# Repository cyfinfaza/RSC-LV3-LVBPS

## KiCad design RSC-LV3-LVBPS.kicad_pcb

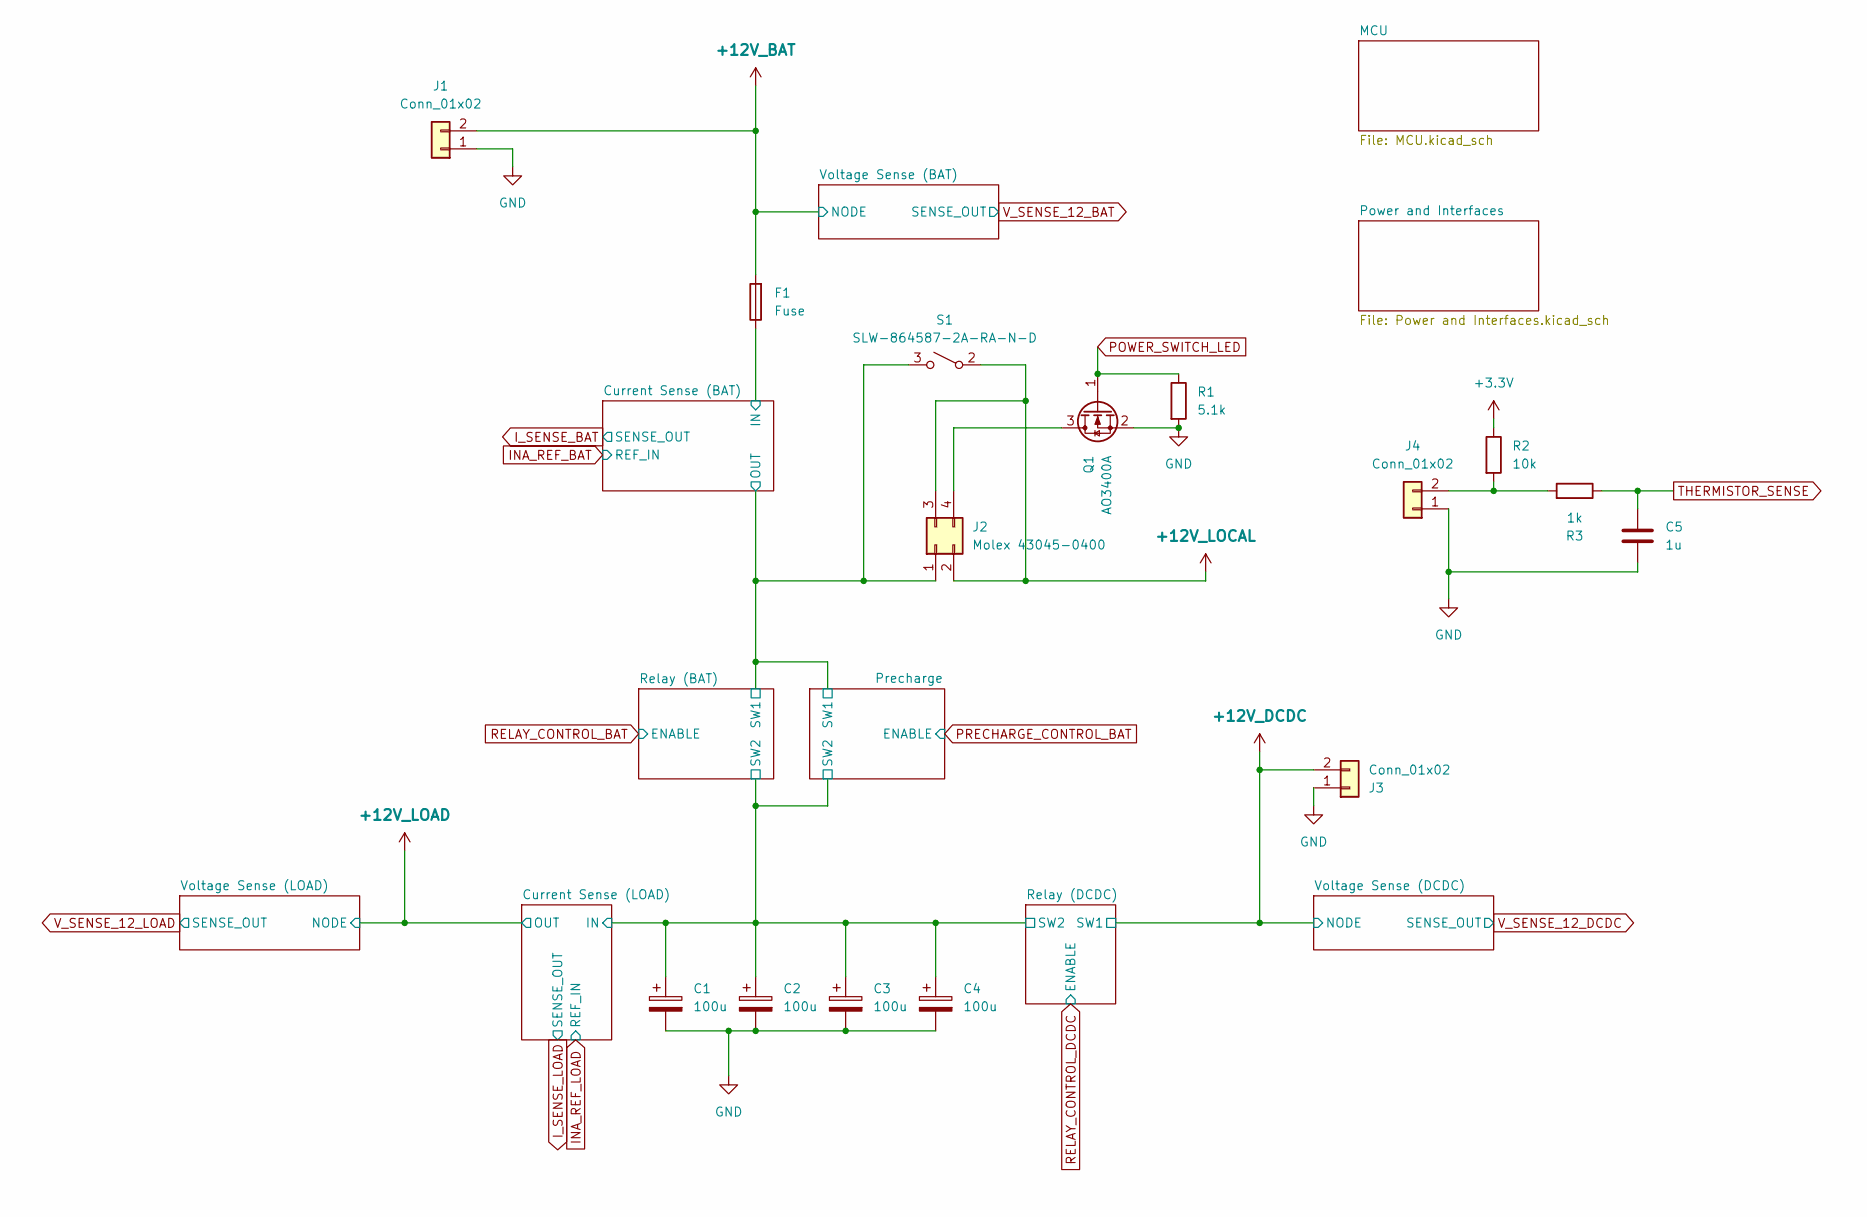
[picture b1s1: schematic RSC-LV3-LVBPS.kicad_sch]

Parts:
C1, C2, C3, C4: 100u; CP_Radial_D6.3mm_P2.50mm
C5: 1u; C_0603_1608Metric_Pad1.08x0.95mm_HandSolder
F1: Fuse; Fuseholder_Blade_Mini_Keystone_3568
J1, J3, J4: Conn_01x02; Molex_Micro-Fit_3.0_43650-0200_1x02_P3.00mm_Horizontal_Vert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
J2: Molex 43045-0400; Molex_Micro-Fit_3.0_43045-0400_2x02_P3.00mm_Horizontal_Vert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
Q1: AO3400A; SOT-23
R1: 5.1k; R_0603_1608Metric_Pad0.98x0.95mm_HandSolder
R2: 10k; R_0603_1608Metric_Pad0.98x0.95mm_HandSolder
R3: 1k; R_0603_1608Metric_Pad0.98x0.95mm_HandSolder
S1: SLW-864587-2A-RA-N-D; SLW8645872ARAND

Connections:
+3.3V: R2.1; also elsewhere on the board
+12V_BAT: F1.2, J1.2; also elsewhere on the board
+12V_DCDC: J3.2; also elsewhere on the board
+12V_LOCAL: J2.2, J2.3, S1.2 (A); also elsewhere on the board
/Current Sense (BAT)/IN: F1.1; also elsewhere on the board
/Current Sense (BAT)/OUT: J2.1, S1.3 (B); also elsewhere on the board
/Current Sense (LOAD)/IN: C1.1, C2.1, C3.1, C4.1; also elsewhere on the board
GND: C1.2, C2.2, C3.2, C4.2, C5.2, J1.1, J3.1, J4.1, Q1.2 (S), R1.2; also elsewhere on the board
unnamed: J2.4, Q1.3 (D)
unnamed: J4.2, R2.2, R3.2
POWER_SWITCH_LED: Q1.1 (G), R1.1; also elsewhere on the board
THERMISTOR_SENSE: C5.1, R3.1; also elsewhere on the board

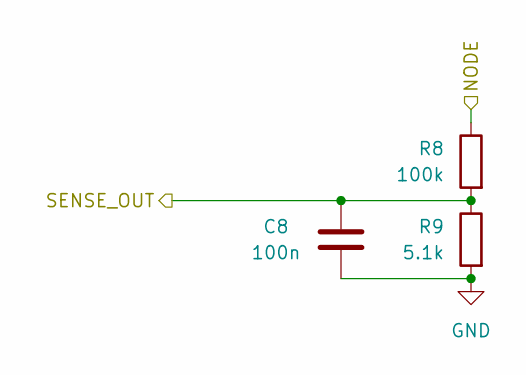
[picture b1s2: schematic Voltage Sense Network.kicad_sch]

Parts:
C8: 100n; C_0603_1608Metric_Pad1.08x0.95mm_HandSolder
R8: 100k; R_0603_1608Metric_Pad0.98x0.95mm_HandSolder
R9: 5.1k; R_0603_1608Metric_Pad0.98x0.95mm_HandSolder

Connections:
+12V_BAT: R8.1; also elsewhere on the board
GND: C8.2, R9.2; also elsewhere on the board
V_SENSE_12_BAT: C8.1, R8.2, R9.1; also elsewhere on the board

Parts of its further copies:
C9, C10: 100n; C_0603_1608Metric_Pad1.08x0.95mm_HandSolder
R12, R14: 100k; R_0603_1608Metric_Pad0.98x0.95mm_HandSolder
R13, R15: 5.1k; R_0603_1608Metric_Pad0.98x0.95mm_HandSolder

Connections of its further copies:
+12V_DCDC: R14.1; also elsewhere on the board
+12V_LOAD: R12.1; also elsewhere on the board
GND: C9.2, C10.2, R13.2, R15.2; also elsewhere on the board
V_SENSE_12_DCDC: C10.1, R14.2, R15.1; also elsewhere on the board
V_SENSE_12_LOAD: C9.1, R12.2, R13.1; also elsewhere on the board

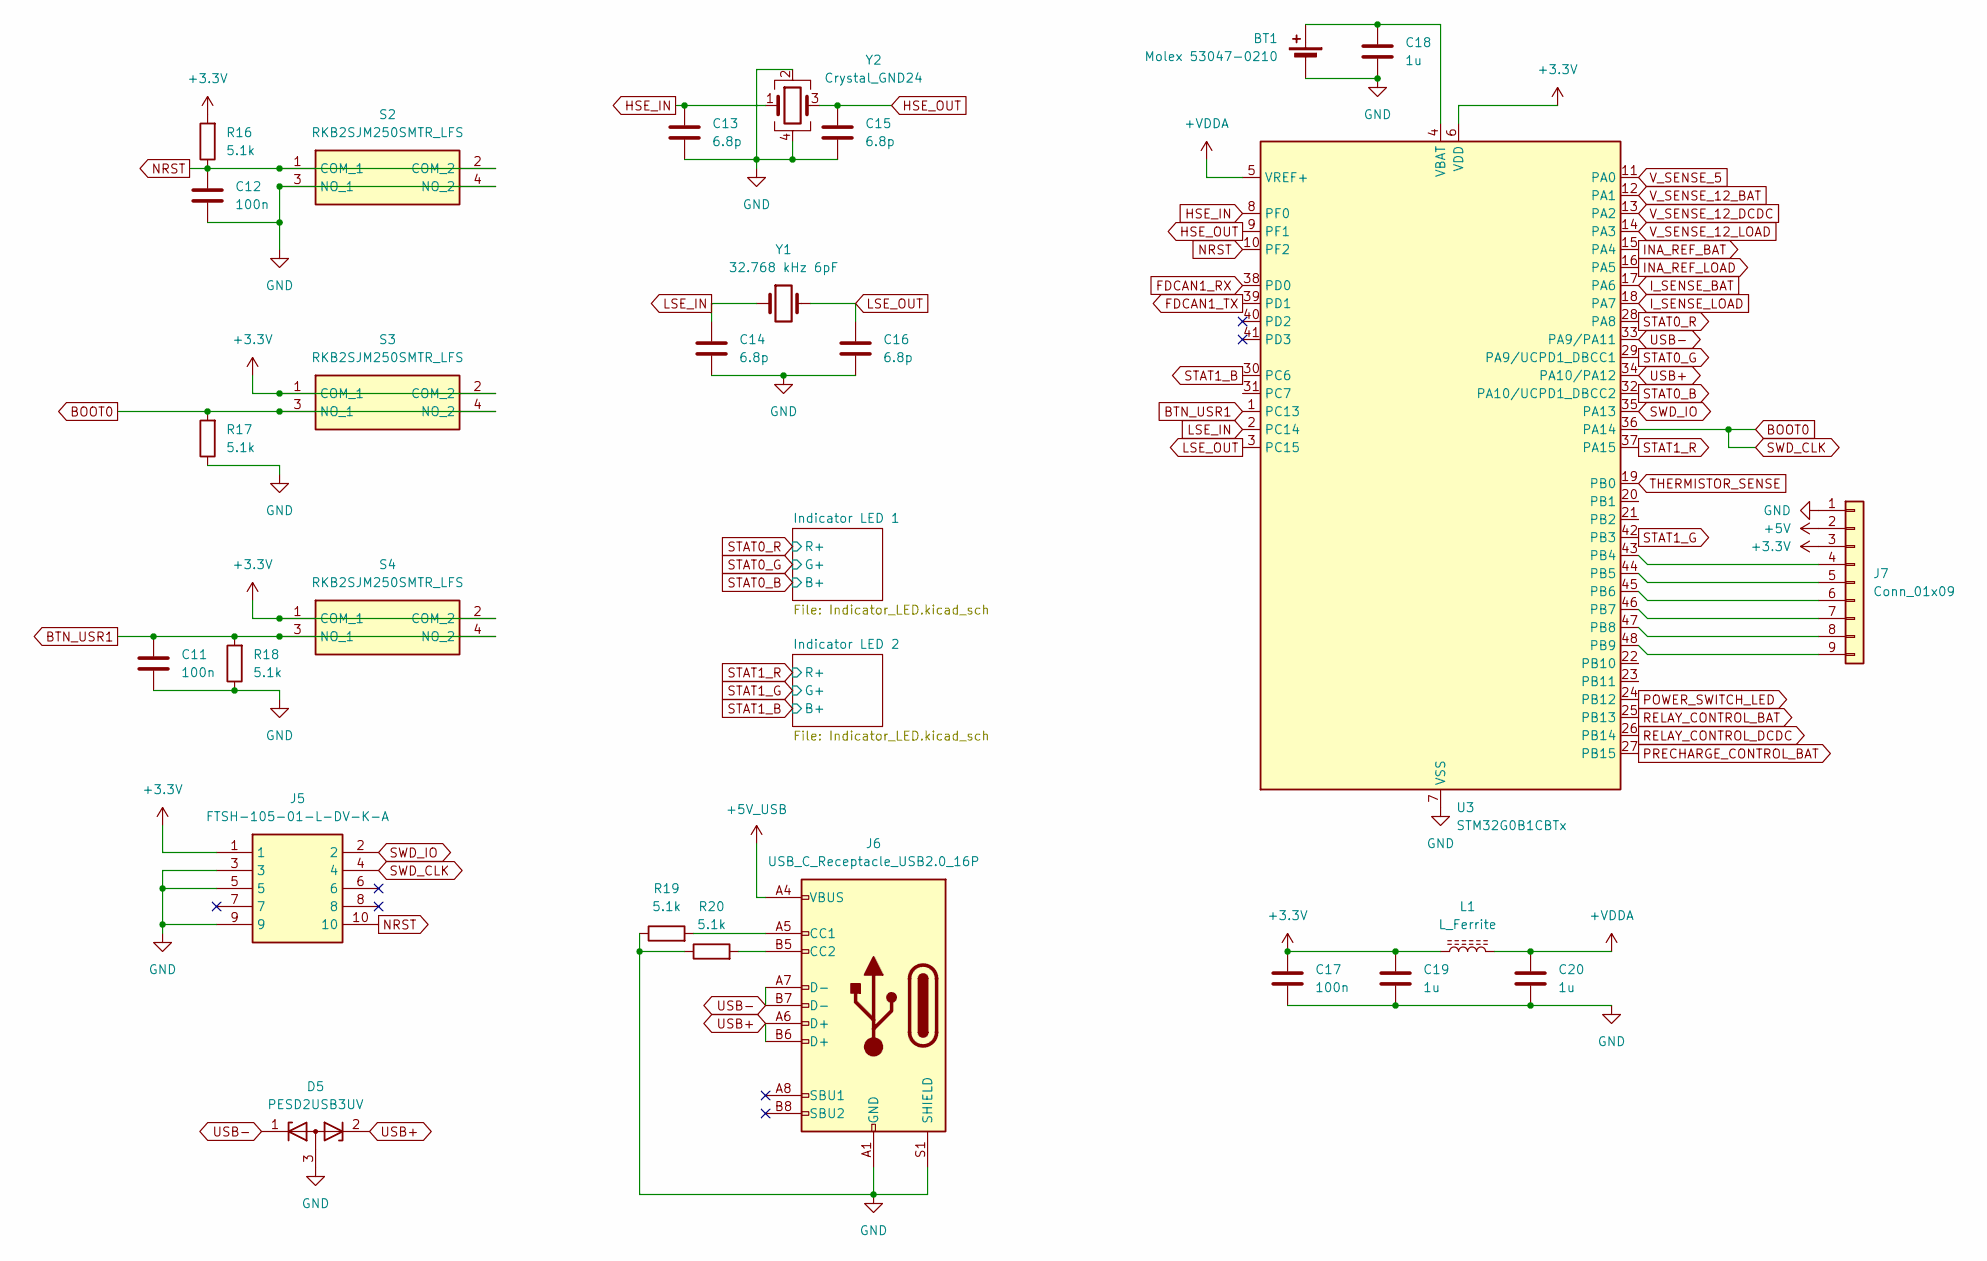
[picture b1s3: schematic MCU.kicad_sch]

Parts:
BT1: Molex 53047-0210; Molex_PicoBlade_53047-0210_1x02_P1.25mm_Vertical
C11, C12, C17: 100n; C_0603_1608Metric_Pad1.08x0.95mm_HandSolder
C13, C14, C15, C16: 6.8p; C_0603_1608Metric_Pad1.08x0.95mm_HandSolder
C18, C19, C20: 1u; C_0603_1608Metric_Pad1.08x0.95mm_HandSolder
D5: PESD2USB3UV; SOT-23W
J5: FTSH-105-01-L-DV-K-A; FTSH-105-XX-YYY-DV-K-A; Mouser Part Number 200-FTSH10501LDVKA
J6: USB_C_Receptacle_USB2.0_16P; USB_C_Receptacle_HRO_TYPE-C-31-M-12
J7: Conn_01x09; PinHeader_1x09_P2.54mm_Vertical
L1: L_Ferrite; L_0603_1608Metric_Pad1.05x0.95mm_HandSolder
R16, R17, R18, R19, R20: 5.1k; R_0603_1608Metric_Pad0.98x0.95mm_HandSolder
S2, S3, S4: RKB2SJM250SMTR_LFS; RKB2SJM250SMTRLFS; Mouser Part Number 611-RKB2SJM250SMTRLF
U3: STM32G0B1CBTx; LQFP-48_7x7mm_P0.5mm
Y1: 32.768 kHz 6pF; Crystal_C26-LF_D2.1mm_L6.5mm_Horizontal
Y2: Crystal_GND24; Crystal_SMD_3225-4Pin_3.2x2.5mm

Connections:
+3.3V: C17.1, C19.1, J5.1, J7.3, L1.1, R16.2, S3.1 (COM_1), S3.2 (COM_2), S4.1 (COM_1), S4.2 (COM_2), U3.6 (VDD); also elsewhere on the board
+5V: J7.2; also elsewhere on the board
+5V_USB: J6.A4 (VBUS), J6.A9 (VBUS), J6.B4 (VBUS), J6.B9 (VBUS); also elsewhere on the board
+VDDA: C20.1, L1.2, U3.5 (VREF+)
BOOT0: J5.4, R17.2, S3.3 (NO_1), S3.4 (NO_2), U3.36 (PA14)
BTN_USR1: C11.1, R18.2, S4.3 (NO_1), S4.4 (NO_2), U3.1 (PC13)
FDCAN1_RX: U3.38 (PD0); also elsewhere on the board
FDCAN1_TX: U3.39 (PD1); also elsewhere on the board
GND: BT1.2 (-), C11.2, C12.2, C13.2, C14.2, C15.2, C16.2, C17.2, C18.2, C19.2, C20.2, D5.3 (A), J5.3, J5.5, J5.9, J6.A1 (GND), J6.A12 (GND), J6.B1 (GND), J6.B12 (GND), J6.S1 (SHIELD), J7.1, R17.1, R18.1, R19.1, R20.1, S2.3 (NO_1), S2.4 (NO_2), U3.7 (VSS), Y2.2, Y2.4; also elsewhere on the board
HSE_IN: C13.1, U3.8 (PF0), Y2.1
HSE_OUT: C15.1, U3.9 (PF1), Y2.3
INA_REF_BAT: U3.15 (PA4); also elsewhere on the board
INA_REF_LOAD: U3.16 (PA5); also elsewhere on the board
I_SENSE_BAT: U3.17 (PA6); also elsewhere on the board
I_SENSE_LOAD: U3.18 (PA7); also elsewhere on the board
LSE_IN: C14.1, U3.2 (PC14), Y1.1
LSE_OUT: C16.1, U3.3 (PC15), Y1.2
NRST: C12.1, J5.10, R16.1, S2.1 (COM_1), S2.2 (COM_2), U3.10 (PF2)
unnamed: BT1.1 (+), C18.1, U3.4 (VBAT)
unnamed: J6.A5 (CC1), R19.2
unnamed: J6.B5 (CC2), R20.2
unnamed: J7.4, U3.43 (PB4)
unnamed: J7.5, U3.44 (PB5)
unnamed: J7.6, U3.45 (PB6)
unnamed: J7.7, U3.46 (PB7)
unnamed: J7.8, U3.47 (PB8)
unnamed: J7.9, U3.48 (PB9)
POWER_SWITCH_LED: U3.24 (PB12); also elsewhere on the board
PRECHARGE_CONTROL_BAT: U3.27 (PB15); also elsewhere on the board
RELAY_CONTROL_BAT: U3.25 (PB13); also elsewhere on the board
RELAY_CONTROL_DCDC: U3.26 (PB14); also elsewhere on the board
STAT0_B: U3.32 (PA10/UCPD1_DBCC2); also elsewhere on the board
STAT0_G: U3.29 (PA9/UCPD1_DBCC1); also elsewhere on the board
STAT0_R: U3.28 (PA8); also elsewhere on the board
STAT1_B: U3.30 (PC6); also elsewhere on the board
STAT1_G: U3.42 (PB3); also elsewhere on the board
STAT1_R: U3.37 (PA15); also elsewhere on the board
SWD_IO: J5.2, U3.35 (PA13)
THERMISTOR_SENSE: U3.19 (PB0); also elsewhere on the board
USB+: D5.2 (K), J6.A6 (D+), J6.B6 (D+), U3.34 (PA10/PA12)
USB-: D5.1 (K), J6.A7 (D-), J6.B7 (D-), U3.33 (PA9/PA11)
V_SENSE_5: U3.11 (PA0); also elsewhere on the board
V_SENSE_12_BAT: U3.12 (PA1); also elsewhere on the board
V_SENSE_12_DCDC: U3.13 (PA2); also elsewhere on the board
V_SENSE_12_LOAD: U3.14 (PA3); also elsewhere on the board

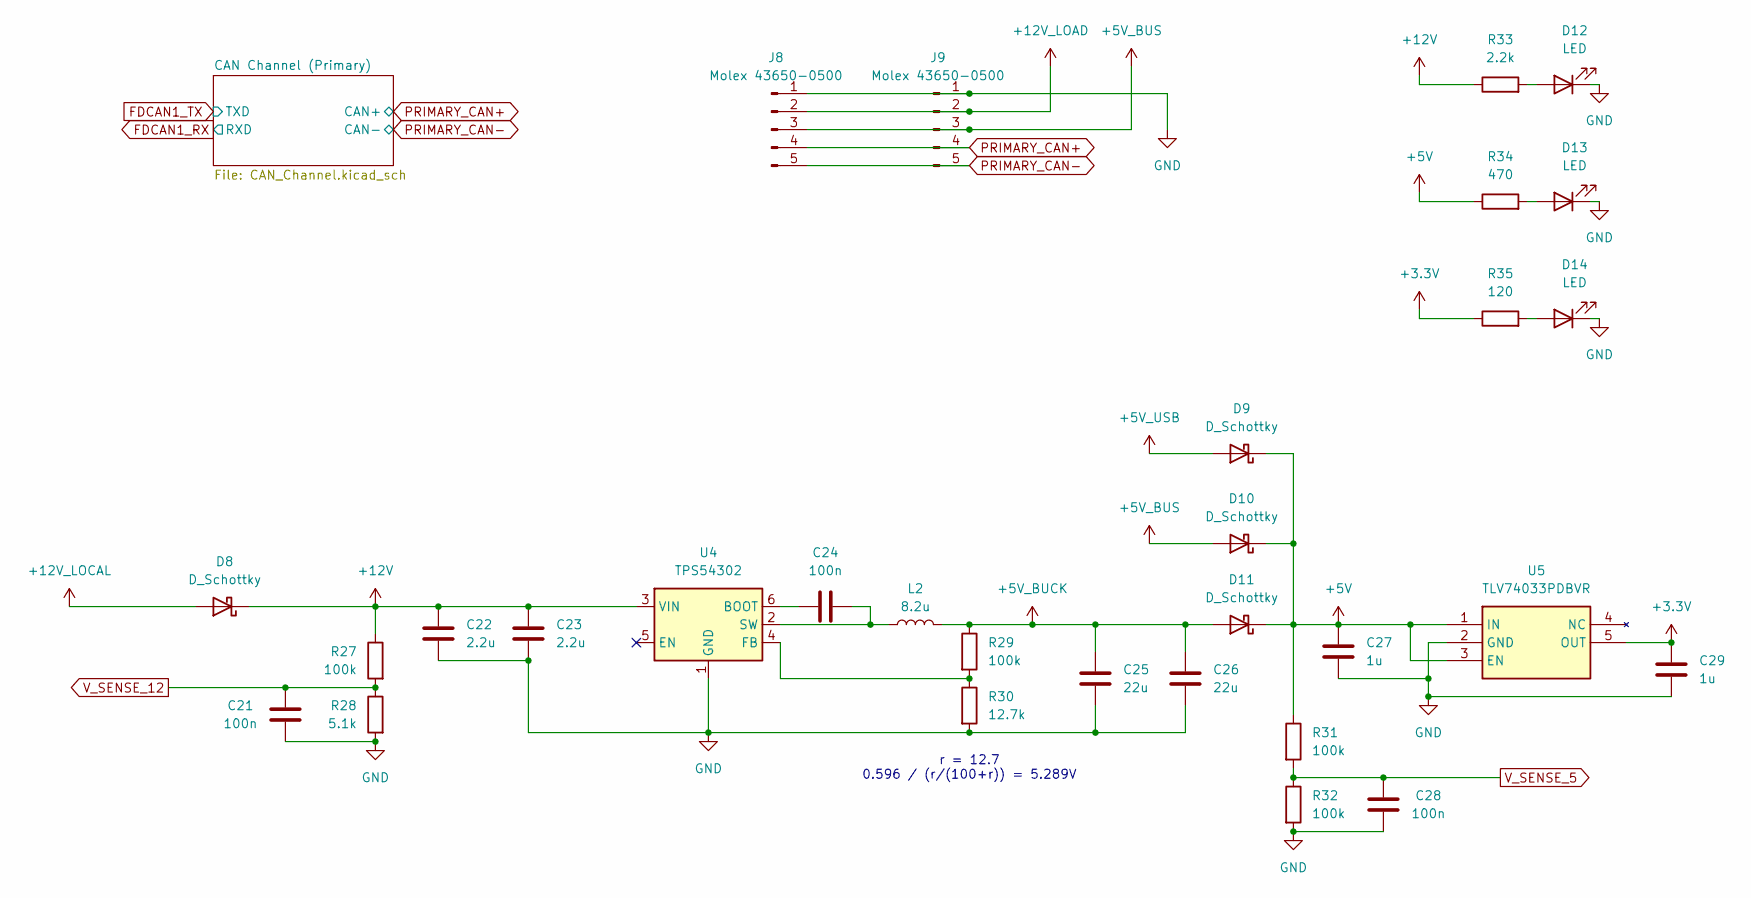
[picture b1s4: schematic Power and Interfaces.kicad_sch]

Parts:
C21, C24, C28: 100n; C_0603_1608Metric_Pad1.08x0.95mm_HandSolder
C22, C23: 2.2u; C_0603_1608Metric_Pad1.08x0.95mm_HandSolder
C25, C26: 22u; C_1206_3216Metric_Pad1.33x1.80mm_HandSolder
C27, C29: 1u; C_0603_1608Metric_Pad1.08x0.95mm_HandSolder
D8, D9, D10, D11: D_Schottky; D_SOD-123F
D12, D13, D14: LED; LED_0603_1608Metric_Pad1.05x0.95mm_HandSolder
J8, J9: Molex 43650-0500; Molex_Micro-Fit_3.0_43650-0500_1x05_P3.00mm_Horizontal_Vert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
L2: 8.2u; L_Abracon_ASPI-4030S
R27, R29, R31, R32: 100k; R_0603_1608Metric_Pad0.98x0.95mm_HandSolder
R28: 5.1k; R_0603_1608Metric_Pad0.98x0.95mm_HandSolder
R30: 12.7k; R_0603_1608Metric_Pad0.98x0.95mm_HandSolder
R33: 2.2k; R_0603_1608Metric_Pad0.98x0.95mm_HandSolder
R34: 470; R_0603_1608Metric_Pad0.98x0.95mm_HandSolder
R35: 120; R_0603_1608Metric_Pad0.98x0.95mm_HandSolder
U4: TPS54302; SOT-23-6_Handsoldering
U5: TLV74033PDBVR; SOT95P280X145-5N; Mouser Part Number 595-TLV74033PDBVR

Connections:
+3.3V: C29.1, R35.1, U5.5 (OUT); also elsewhere on the board
+5V: C27.1, D9.1 (K), D10.1 (K), D11.1 (K), R31.1, R34.1, U5.1 (IN), U5.3 (EN); also elsewhere on the board
+5V_BUCK: C25.1, C26.1, D11.2 (A), L2.2, R29.1
+5V_BUS: D10.2 (A), J8.3, J9.3
+5V_USB: D9.2 (A); also elsewhere on the board
+12V: C22.1, C23.1, D8.1 (K), R27.1, R33.1, U4.3 (VIN)
+12V_LOAD: J8.2, J9.2; also elsewhere on the board
+12V_LOCAL: D8.2 (A); also elsewhere on the board
GND: C21.2, C22.2, C23.2, C25.2, C26.2, C27.2, C28.2, C29.2, D12.1 (K), D13.1 (K), D14.1 (K), J8.1, J9.1, R28.2, R30.2, R32.2, U4.1 (GND), U5.2 (GND); also elsewhere on the board
unnamed: D12.2 (A), R33.2
unnamed: D13.2 (A), R34.2
unnamed: D14.2 (A), R35.2
unnamed: C24.1, U4.6 (BOOT)
unnamed: R29.2, R30.1, U4.4 (FB)
unnamed: C24.2, L2.1, U4.2 (SW)
PRIMARY_CAN+: J8.4, J9.4; also elsewhere on the board
PRIMARY_CAN-: J8.5, J9.5; also elsewhere on the board
V_SENSE_5: C28.1, R31.2, R32.1; also elsewhere on the board
V_SENSE_12: C21.1, R27.2, R28.1

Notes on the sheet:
r = 12.7 0.596 / (r/(100+r)) = 5.289V

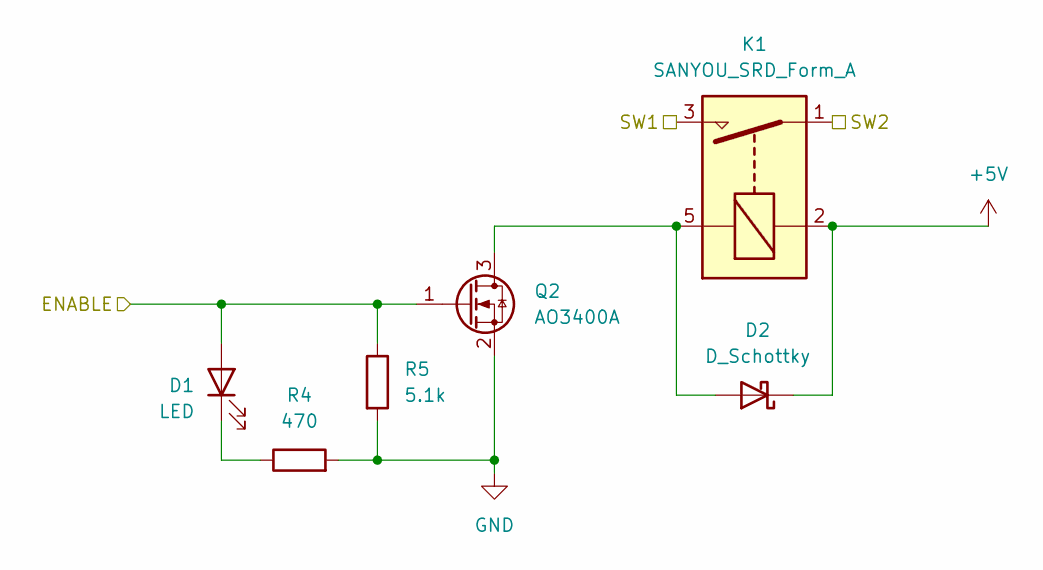
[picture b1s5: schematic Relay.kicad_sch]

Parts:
D1: LED; LED_0603_1608Metric_Pad1.05x0.95mm_HandSolder
D2: D_Schottky; D_SOD-123F
K1: SANYOU_SRD_Form_A; Relay_SPST_SANYOU_SRD_Series_Form_A
Q2: AO3400A; SOT-23
R4: 470; R_0603_1608Metric_Pad0.98x0.95mm_HandSolder
R5: 5.1k; R_0603_1608Metric_Pad0.98x0.95mm_HandSolder

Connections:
+5V: D2.1 (K), K1.2; also elsewhere on the board
+12V_DCDC: K1.3; also elsewhere on the board
/Current Sense (LOAD)/IN: K1.1; also elsewhere on the board
GND: Q2.2 (S), R4.2, R5.2; also elsewhere on the board
unnamed: D1.1 (K), R4.1
unnamed: D2.2 (A), K1.5, Q2.3 (D)
RELAY_CONTROL_DCDC: D1.2 (A), Q2.1 (G), R5.1; also elsewhere on the board

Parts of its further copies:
D3: LED; LED_0603_1608Metric_Pad1.05x0.95mm_HandSolder
D4: D_Schottky; D_SOD-123F
K2: SANYOU_SRD_Form_A; Relay_SPST_SANYOU_SRD_Series_Form_A
Q3: AO3400A; SOT-23
R10: 470; R_0603_1608Metric_Pad0.98x0.95mm_HandSolder
R11: 5.1k; R_0603_1608Metric_Pad0.98x0.95mm_HandSolder

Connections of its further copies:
+5V: D4.1 (K), K2.2; also elsewhere on the board
/Current Sense (BAT)/OUT: K2.3; also elsewhere on the board
/Current Sense (LOAD)/IN: K2.1; also elsewhere on the board
GND: Q3.2 (S), R10.2, R11.2; also elsewhere on the board
unnamed: D3.1 (K), R10.1
unnamed: D4.2 (A), K2.5, Q3.3 (D)
RELAY_CONTROL_BAT: D3.2 (A), Q3.1 (G), R11.1; also elsewhere on the board

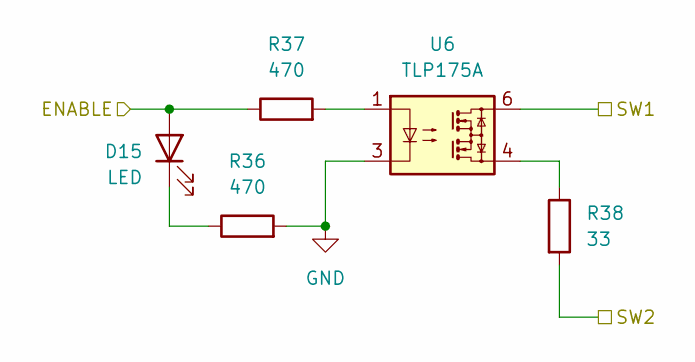
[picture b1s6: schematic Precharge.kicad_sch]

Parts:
D15: LED; LED_0603_1608Metric_Pad1.05x0.95mm_HandSolder
R36, R37: 470; R_0603_1608Metric_Pad0.98x0.95mm_HandSolder
R38: 33; R_2512_6332Metric
U6: TLP175A; Toshiba_SOIC-4-6_4.4x3.6mm_P1.27mm

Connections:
/Current Sense (BAT)/OUT: U6.6; also elsewhere on the board
/Current Sense (LOAD)/IN: R38.2; also elsewhere on the board
GND: R36.2, U6.3; also elsewhere on the board
unnamed: D15.1 (K), R36.1
unnamed: R37.2, U6.1
unnamed: R38.1, U6.4
PRECHARGE_CONTROL_BAT: D15.2 (A), R37.1; also elsewhere on the board

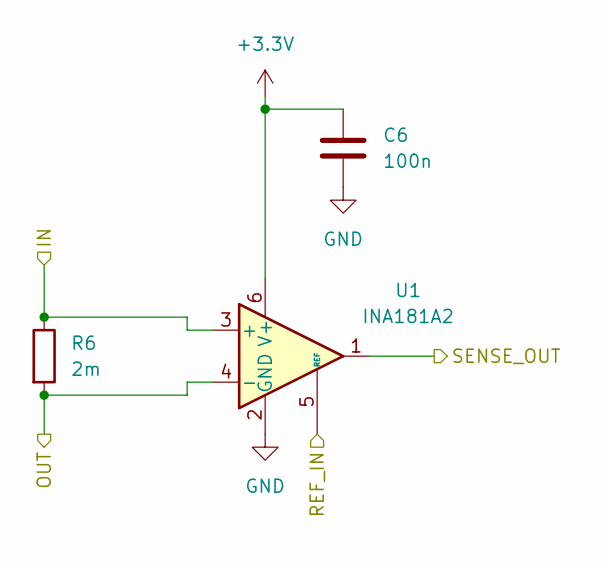
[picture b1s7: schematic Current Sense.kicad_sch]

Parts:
C6: 100n; C_0603_1608Metric_Pad1.08x0.95mm_HandSolder
R6: 2m; R_1206_3216Metric_Pad1.30x1.75mm_HandSolder
U1: INA181A2; SOT-23-6_Handsoldering

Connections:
+3.3V: C6.1, U1.6 (V+); also elsewhere on the board
/Current Sense (BAT)/IN: R6.1, U1.3 (+); also elsewhere on the board
/Current Sense (BAT)/OUT: R6.2, U1.4 (-); also elsewhere on the board
GND: C6.2, U1.2 (GND); also elsewhere on the board
INA_REF_BAT: U1.5 (REF); also elsewhere on the board
I_SENSE_BAT: U1.1; also elsewhere on the board

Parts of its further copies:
C7: 100n; C_0603_1608Metric_Pad1.08x0.95mm_HandSolder
R7: 2m; R_1206_3216Metric_Pad1.30x1.75mm_HandSolder
U2: INA181A2; SOT-23-6_Handsoldering

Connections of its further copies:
+3.3V: C7.1, U2.6 (V+); also elsewhere on the board
+12V_LOAD: R7.2, U2.4 (-); also elsewhere on the board
/Current Sense (LOAD)/IN: R7.1, U2.3 (+); also elsewhere on the board
GND: C7.2, U2.2 (GND); also elsewhere on the board
INA_REF_LOAD: U2.5 (REF); also elsewhere on the board
I_SENSE_LOAD: U2.1; also elsewhere on the board

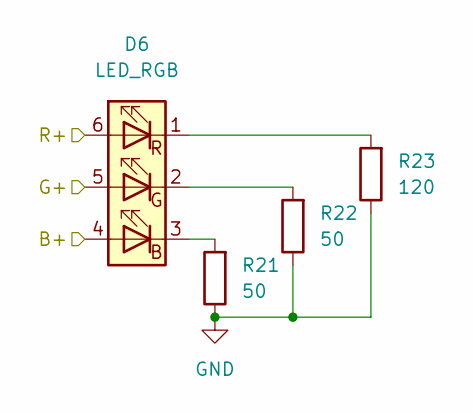
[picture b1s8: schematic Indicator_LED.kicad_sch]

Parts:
D6: LED_RGB; LED_RGB_5050-6
R21, R22: 50; R_0603_1608Metric_Pad0.98x0.95mm_HandSolder
R23: 120; R_0603_1608Metric_Pad0.98x0.95mm_HandSolder

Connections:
GND: R21.1, R22.1, R23.1; also elsewhere on the board
unnamed: D6.3 (BK), R21.2
unnamed: D6.2 (GK), R22.2
unnamed: D6.1 (RK), R23.2
STAT0_B: D6.4 (BA); also elsewhere on the board
STAT0_G: D6.5 (GA); also elsewhere on the board
STAT0_R: D6.6 (RA); also elsewhere on the board

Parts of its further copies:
D7: LED_RGB; LED_RGB_5050-6
R24, R25: 50; R_0603_1608Metric_Pad0.98x0.95mm_HandSolder
R26: 120; R_0603_1608Metric_Pad0.98x0.95mm_HandSolder

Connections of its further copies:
GND: R24.1, R25.1, R26.1; also elsewhere on the board
unnamed: D7.3 (BK), R24.2
unnamed: D7.2 (GK), R25.2
unnamed: D7.1 (RK), R26.2
STAT1_B: D7.4 (BA); also elsewhere on the board
STAT1_G: D7.5 (GA); also elsewhere on the board
STAT1_R: D7.6 (RA); also elsewhere on the board

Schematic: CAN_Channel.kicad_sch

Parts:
C30, C31: 100n; C_0603_1608Metric_Pad1.08x0.95mm_HandSolder
C32: 1u; C_0603_1608Metric_Pad1.08x0.95mm_HandSolder
R39: 120; R_0603_1608Metric_Pad0.98x0.95mm_HandSolder
S5: SLW-864587-2A-RA-N-D; SLW8645872ARAND; Mouser Part Number 179-SLW8645872ARAND
U7: TJA1051T-3; SOIC-8_3.9x4.9mm_P1.27mm

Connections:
+3.3V: C30.1, U7.5 (VIO); also elsewhere on the board
+5V: C31.1, C32.1, U7.3 (VCC); also elsewhere on the board
FDCAN1_RX: U7.4 (RXD); also elsewhere on the board
FDCAN1_TX: U7.1 (TXD); also elsewhere on the board
GND: C30.2, C31.2, C32.2, U7.2 (GND), U7.8 (S); also elsewhere on the board
unnamed: R39.2, S5.3 (NO)
PRIMARY_CAN+: R39.1, U7.7 (CANH); also elsewhere on the board
PRIMARY_CAN-: S5.2 (COM), U7.6 (CANL); also elsewhere on the board

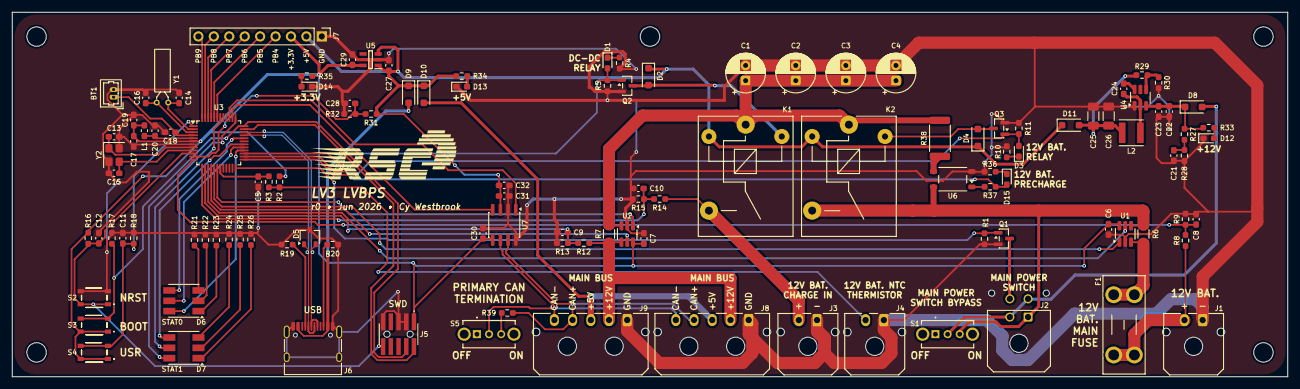
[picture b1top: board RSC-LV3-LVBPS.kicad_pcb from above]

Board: 2 copper layers, 210.0 x 60.0 mm, 118 parts (0 on the bottom side), 80 nets.

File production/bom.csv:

Designator,Footprint,Quantity,Value,LCSC Part #
BT1,Molex_PicoBlade_53047-0210_1x02_P1.25mm_Vertical,1,Molex 53047-0210,
"C1, C2, C3, C4",CP_Radial_D6.3mm_P2.50mm,4,100u,
"C10, C11, C12, C17, C21, C24, C28, C30, C31, C6, C7, C8, C9",0603,13,100n,
"C13, C14, C15, C16",0603,4,6.8p,
"C18, C19, C20, C27, C29, C32, C5",0603,7,1u,
"C22, C23",0603,2,2.2u,
"C25, C26",1206,2,22u,
"D1, D12, D13, D14, D15, D3",0603,6,LED,
"D10, D11, D2, D4, D8, D9",D_SOD-123F,6,D_Schottky,
D5,SOT-23W,1,PESD2USB3UV,
"D6, D7",LED_RGB_5050-6,2,LED_RGB,
F1,Fuseholder_Blade_Mini_Keystone_3568,1,Fuse,
"J1, J3, J4",Molex_Micro-Fit_3.0_43650-0200_1x02_P3.00mm_Horizontal_VerticalCompatible,3,Conn_01x02,
J2,Molex_Micro-Fit_3.0_43045-0400_2x02_P3.00mm_Horizontal_VerticalCompatible,1,Molex 43045-0400,
J5,FTSH-105-XX-YYY-DV-K-A,1,FTSH-105-01-L-DV-K-A,
J6,USB_C_Receptacle_HRO_TYPE-C-31-M-12,1,USB_C_Receptacle_USB2.0_16P,
J7,PinHeader_1x09_P2.54mm_Vertical,1,Conn_01x09,
"J8, J9",Molex_Micro-Fit_3.0_43650-0500_1x05_P3.00mm_Horizontal_VerticalCompatible,2,Molex 43650-0500,
"K1, K2",Relay_SPST_SANYOU_SRD_Series_Form_A,2,SANYOU_SRD_Form_A,
L1,0603,1,L_Ferrite,
L2,L_Abracon_ASPI-4030S,1,8.2u,
"Q1, Q2, Q3",SOT-23,3,AO3400A,
"R1, R11, R13, R15, R16, R17, R18, R19, R20, R28, R5, R9",0603,12,5.1k,
"R10, R34, R36, R37, R4",0603,5,470,
"R12, R14, R27, R29, R31, R32, R8",0603,7,100k,
R2,0603,1,10k,
"R21, R22, R24, R25",0603,4,50,
"R23, R26, R35, R39",0603,4,120,
R3,0603,1,1k,
R30,0603,1,12.7k,
R33,0603,1,2.2k,
R38,2512,1,33,
"R6, R7",1206,2,2m,
"S1, S5",SLW8645872ARAND,2,SLW-864587-2A-RA-N-D,
"S2, S3, S4",RKB2SJM250SMTRLFS,3,RKB2SJM250SMTR_LFS,
"U1, U2",SOT-23-6_Handsoldering,2,INA181A2,
U3,LQFP-48_7x7mm_P0.5mm,1,STM32G0B1CBTx,
U4,SOT-23-6_Handsoldering,1,TPS54302,
U5,SOT95P280X145-5N,1,TLV74033PDBVR,
U6,Toshiba_SOIC-4-6_4.4x3.6mm_P1.27mm,1,TLP175A,
U7,SOIC-8_3.9x4.9mm_P1.27mm,1,TJA1051T-3,
Y1,Crystal_C26-LF_D2.1mm_L6.5mm_Horizontal,1,32.768 kHz 6pF,
Y2,Crystal_SMD_3225-4Pin_3.2x2.5mm,1,Crystal_GND24,

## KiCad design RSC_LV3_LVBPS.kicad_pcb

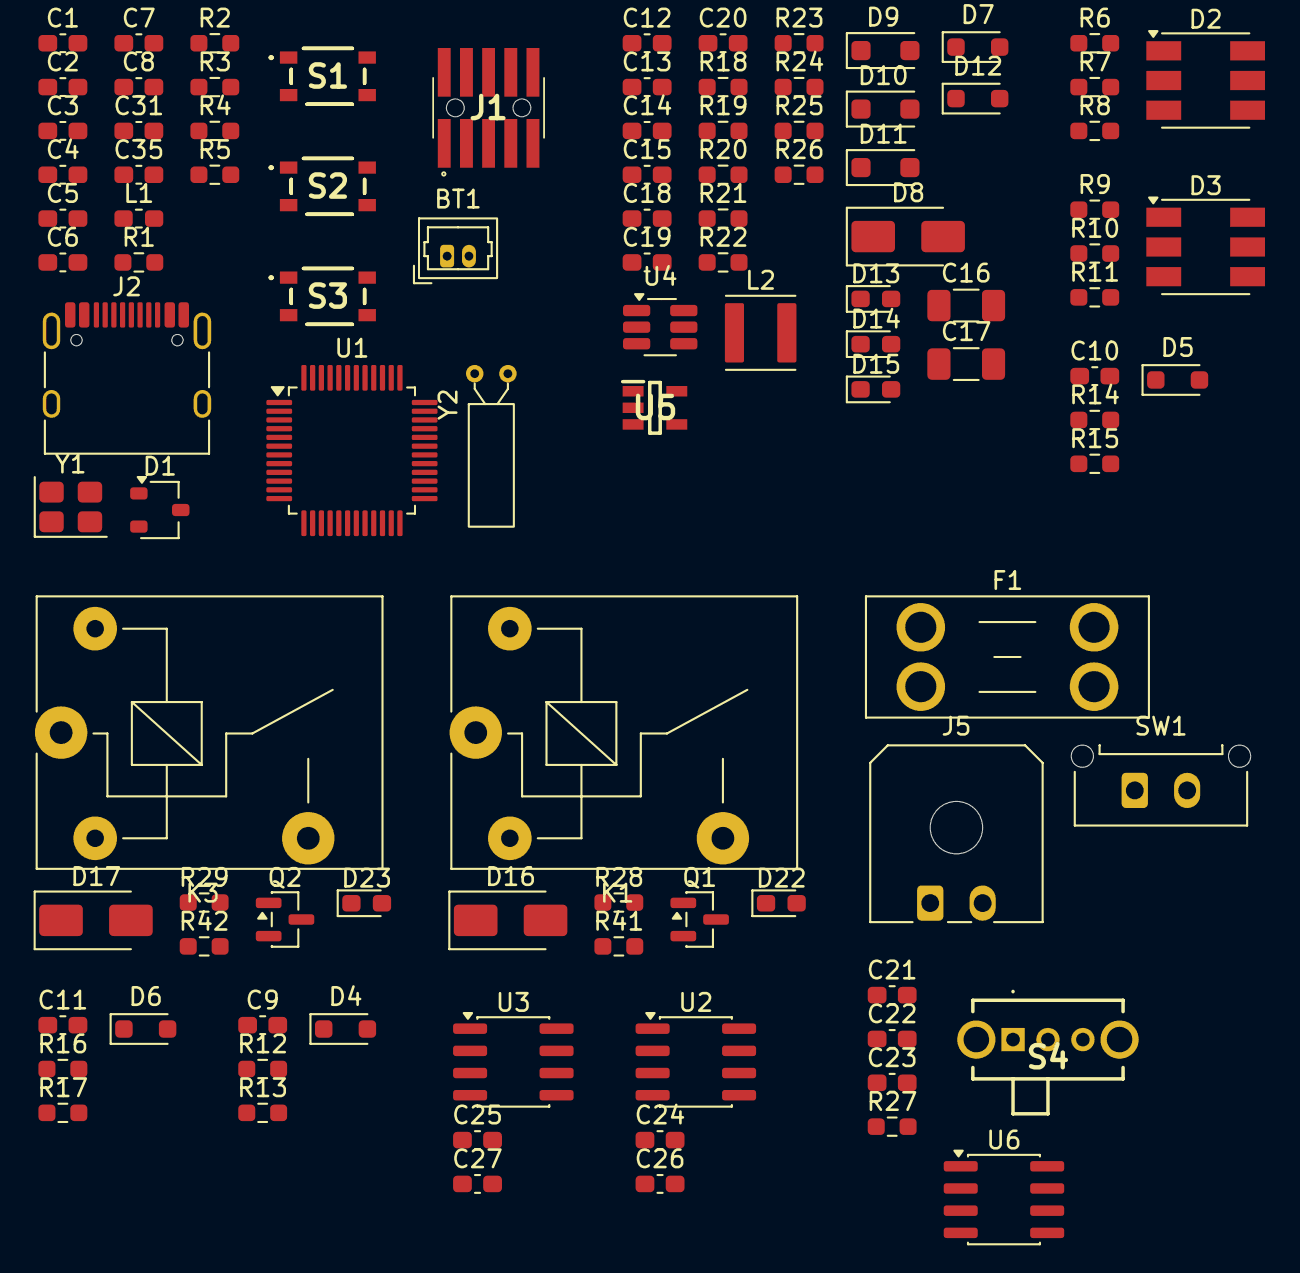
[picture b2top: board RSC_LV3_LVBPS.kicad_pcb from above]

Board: 2 copper layers, 103 parts (0 on the bottom side), 62 nets, no tracks yet.

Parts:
BT1: Molex 53047-0210; Molex_PicoBlade_53047-0210_1x02_P1.25mm_Vertical
C1, C2, C5, C9, C10, C11, C12, C15, C19, C21, C22, C24, C25: 100n; C_0603_1608Metric_Pad1.08x0.95mm_HandSolder
C3, C4, C8, C31: 6.8p; C_0603_1608Metric_Pad1.08x0.95mm_HandSolder
C6, C7, C18, C20, C23, C35: 1u; C_0603_1608Metric_Pad1.08x0.95mm_HandSolder
C13, C14: 2.2u; C_0603_1608Metric_Pad1.08x0.95mm_HandSolder
C16, C17: 22u; C_1206_3216Metric_Pad1.33x1.80mm_HandSolder
C26, C27: 1n; C_0603_1608Metric_Pad1.08x0.95mm_HandSolder
D1: PESD2USB3UV; SOT-23W
D2, D3: LED_RGB; LED_RGB_5050-6
D4, D5, D6, D7, D12: D_Zener; D_SOD-323_HandSoldering
D8, D16, D17: D_Schottky; D_SMA
D9, D10, D11: D_Schottky; D_SOD-123F
D13, D14, D15, D22, D23: LED; LED_0603_1608Metric_Pad1.05x0.95mm_HandSolder
F1: Fuse; Fuseholder_Blade_Mini_Keystone_3568
J1: FTSH-105-01-L-DV-K-A; FTSH-105-XX-YYY-DV-K-A
J2: USB_C_Receptacle_USB2.0_16P; USB_C_Receptacle_HRO_TYPE-C-31-M-12
J5: Conn_01x02; Molex_Micro-Fit_3.0_43650-0200_1x02_P3.00mm_Horizontal
K1, K3: Relay_SPST-NO; Relay_SPST_SANYOU_SRD_Series_Form_A
L1: L_Ferrite; L_0603_1608Metric_Pad1.05x0.95mm_HandSolder
L2: 8.2u; L_Abracon_ASPI-4030S
Q1, Q2: AO3400A; SOT-23
R1, R2, R3, R4, R5, R13, R15, R17, R19, R28, R29: 5.1k; R_0603_1608Metric_Pad0.98x0.95mm_HandSolder
R6, R7, R9, R10: 50; R_0603_1608Metric_Pad0.98x0.95mm_HandSolder
R8, R11, R26, R27: 120; R_0603_1608Metric_Pad0.98x0.95mm_HandSolder
R12, R14, R16, R18, R20, R22, R23: 100k; R_0603_1608Metric_Pad0.98x0.95mm_HandSolder
R21: 12.7k; R_0603_1608Metric_Pad0.98x0.95mm_HandSolder
R24: 2.2k; R_0603_1608Metric_Pad0.98x0.95mm_HandSolder
R25, R41, R42: 470; R_0603_1608Metric_Pad0.98x0.95mm_HandSolder
S1, S2, S3: RKB2SJM250SMTR_LFS; RKB2SJM250SMTRLFS
S4: SLW-864587-2A-RA-N-D; SLW8645872ARAND
SW1: SW_SPST; Molex_Micro-Fit_3.0_43650-0215_1x02_P3.00mm_Vertical
U1: STM32G0B1CBTx; LQFP-48_7x7mm_P0.5mm
U2, U3: ACS711xLCTR-12AB; SOIC-8_3.9x4.9mm_P1.27mm
U4: TPS54302; SOT-23-6_Handsoldering
U5: TLV74033PDBVR; SOT95P280X145-5N
U6: TJA1051T-3; SOIC-8_3.9x4.9mm_P1.27mm
Y1: Crystal_GND24; Crystal_SMD_3225-4Pin_3.2x2.5mm
Y2: 32.768 kHz 6pF; Crystal_C26-LF_D2.1mm_L6.5mm_Horizontal

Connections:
+3.3V: C5.1, C6.1, C20.1, C21.1, C24.1, C25.1, J1.1, L1.1, R1.2, R26.1, S2.1 (COM_1), S2.2 (COM_2), S3.1 (COM_1), S3.2 (COM_2), U1.6 (VDD), U2.8 (VCC), U3.8 (VCC), U5.5 (OUT), U6.5 (VIO)
+5V: C18.1, C22.1, C23.1, D9.1 (K), D10.1 (K), D11.1 (K), D16.1 (K), D17.1 (K), R22.1, R25.1, U5.1 (IN), U5.3 (EN), U6.3 (VCC)
+5V_BUCK: C16.1, C17.1, D11.2 (A), L2.2, R20.1
+5V_USB: D9.2 (A), J2.A4 (VBUS), J2.A9 (VBUS), J2.B4 (VBUS), J2.B9 (VBUS)
+12V: C13.1, C14.1, D8.1 (K), R18.1, R24.1, U4.3 (VIN)
+12V_BAT: F1.2, J5.2, R12.1
+12V_LOAD: R14.1, U3.3 (IP-), U3.4 (IP-)
+12V_LOCAL: D8.2 (A), SW1.1 (A)
+VDDA: C7.1, L1.2, U1.5 (VREF+)
/Current Sense (BAT)/IN: F1.1, U2.1 (IP+), U2.2 (IP+)
/Current Sense (BAT)/OUT: SW1.2 (B), U2.3 (IP-), U2.4 (IP-)
/Current Sense (LOAD)/IN: U3.1 (IP+), U3.2 (IP+)
BOOT0: J1.4, R2.2, S2.3 (NO_1), S2.4 (NO_2), U1.36 (PA14)
BTN_USR1: C1.1, R3.2, S3.3 (NO_1), S3.4 (NO_2), U1.1 (PC13)
FDCAN1_RX: U1.38 (PD0), U6.4 (RXD)
FDCAN1_TX: U1.39 (PD1), U6.1 (TXD)
GND: BT1.2 (-), C1.2, C2.2, C3.2, C4.2, C5.2, C6.2, C7.2, C8.2, C9.2, C10.2, C11.2, C12.2, C13.2, C14.2, C16.2, C17.2, C18.2, C19.2, C20.2, C21.2, C22.2, C23.2, C24.2, C25.2, C26.2, C27.2, C31.2, C35.2, D1.3 (A), D4.2 (A), D5.2 (A), D6.2 (A), D7.2 (A), D12.2 (A), D13.1 (K), D14.1 (K), D15.1 (K), J1.3, J1.5, J1.9, J2.A1 (GND), J2.A12 (GND), J2.B1 (GND), J2.B12 (GND), J5.1, Q1.2 (S), Q2.2 (S), R2.1, R3.1, R4.1, R5.1, R6.1, R7.1, R8.1, R9.1, R10.1, R11.1, R13.2, R15.2, R17.2, R19.2, R21.2, R23.2, R28.2, R29.2, R41.2, R42.2, S1.3 (NO_1), S1.4 (NO_2), U1.7 (VSS), U2.5 (GND), U3.5 (GND), U4.1 (GND), U5.2 (GND), U6.2 (GND), U6.8 (S), Y1.2, Y1.4
HSE_IN: C3.1, U1.8 (PF0), Y1.1
HSE_OUT: C4.1, U1.9 (PF1), Y1.3
I_SENSE_BAT: C26.1, U1.15 (PA4), U2.7 (VIOUT)
I_SENSE_LOAD: C27.1, U1.16 (PA5), U3.7 (VIOUT)
LSE_IN: C8.1, U1.2 (PC14), Y2.1
LSE_OUT: C31.1, U1.3 (PC15), Y2.2
NRST: C2.1, J1.10, R1.1, S1.1 (COM_1), S1.2 (COM_2), U1.10 (PF2)
unnamed: BT1.1 (+), C35.1, U1.4 (VBAT)
unnamed: D2.3 (BK), R6.2
unnamed: D2.2 (GK), R7.2
unnamed: D2.1 (RK), R8.2
unnamed: D3.3 (BK), R9.2
unnamed: D3.2 (GK), R10.2
unnamed: D3.1 (RK), R11.2
unnamed: D13.2 (A), R24.2
unnamed: D14.2 (A), R25.2
unnamed: D15.2 (A), R26.2
unnamed: D16.2 (A), Q1.3 (D)
unnamed: D17.2 (A), Q2.3 (D)
unnamed: D22.1 (K), R41.1
unnamed: D23.1 (K), R42.1
unnamed: J2.A5 (CC1), R4.2
unnamed: J2.B5 (CC2), R5.2
unnamed: R27.2, S4.3 (NO)
unnamed: C15.1, U4.6 (BOOT)
unnamed: R20.2, R21.1, U4.4 (FB)
unnamed: C15.2, L2.1, U4.2 (SW)
PRIMARY_CAN+: R27.1, U6.7 (CANH)
PRIMARY_CAN-: S4.2 (COM), U6.6 (CANL)
RELAY_CONTROL_BAT: D23.2 (A), Q2.1 (G), R29.1, U1.19 (PB0)
RELAY_CONTROL_DCDC: D22.2 (A), Q1.1 (G), R28.1, U1.20 (PB1)
STAT0_B: D2.4 (BA), U1.32 (PA10/UCPD1_DBCC2)
STAT0_G: D2.5 (GA), U1.29 (PA9/UCPD1_DBCC1)
STAT0_R: D2.6 (RA), U1.28 (PA8)
STAT1_B: D3.4 (BA), U1.30 (PC6)
STAT1_G: D3.5 (GA), U1.42 (PB3)
STAT1_R: D3.6 (RA), U1.37 (PA15)
SWD_IO: J1.2, U1.35 (PA13)
USB+: D1.2 (K), J2.A6 (D+), J2.B6 (D+), U1.34 (PA10/PA12)
USB-: D1.1 (K), J2.A7 (D-), J2.B7 (D-), U1.33 (PA9/PA11)
V_SENSE_5: C19.1, D12.1 (K), R22.2, R23.1, U1.11 (PA0)
V_SENSE_12: C12.1, D7.1 (K), R18.2, R19.1
V_SENSE_12_BAT: C9.1, D4.1 (K), R12.2, R13.1, U1.12 (PA1)
V_SENSE_12_DCDC: C11.1, D6.1 (K), R16.2, R17.1, U1.13 (PA2)
V_SENSE_12_LOAD: C10.1, D5.1 (K), R14.2, R15.1, U1.14 (PA3)

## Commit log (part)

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2026-06-03 add MCU and power circuits
2026-06-03 rename project to use dashes instead of underscores for consistency
2026-06-11 more schematic work and initial layout
2026-06-13 more layout work
2026-06-14 schematic changes and initial routing
2026-06-15 finished layout, routing, and silkscreen
2026-06-16 minor layout and silkscreen tweaks
2026-06-22 r0 final
